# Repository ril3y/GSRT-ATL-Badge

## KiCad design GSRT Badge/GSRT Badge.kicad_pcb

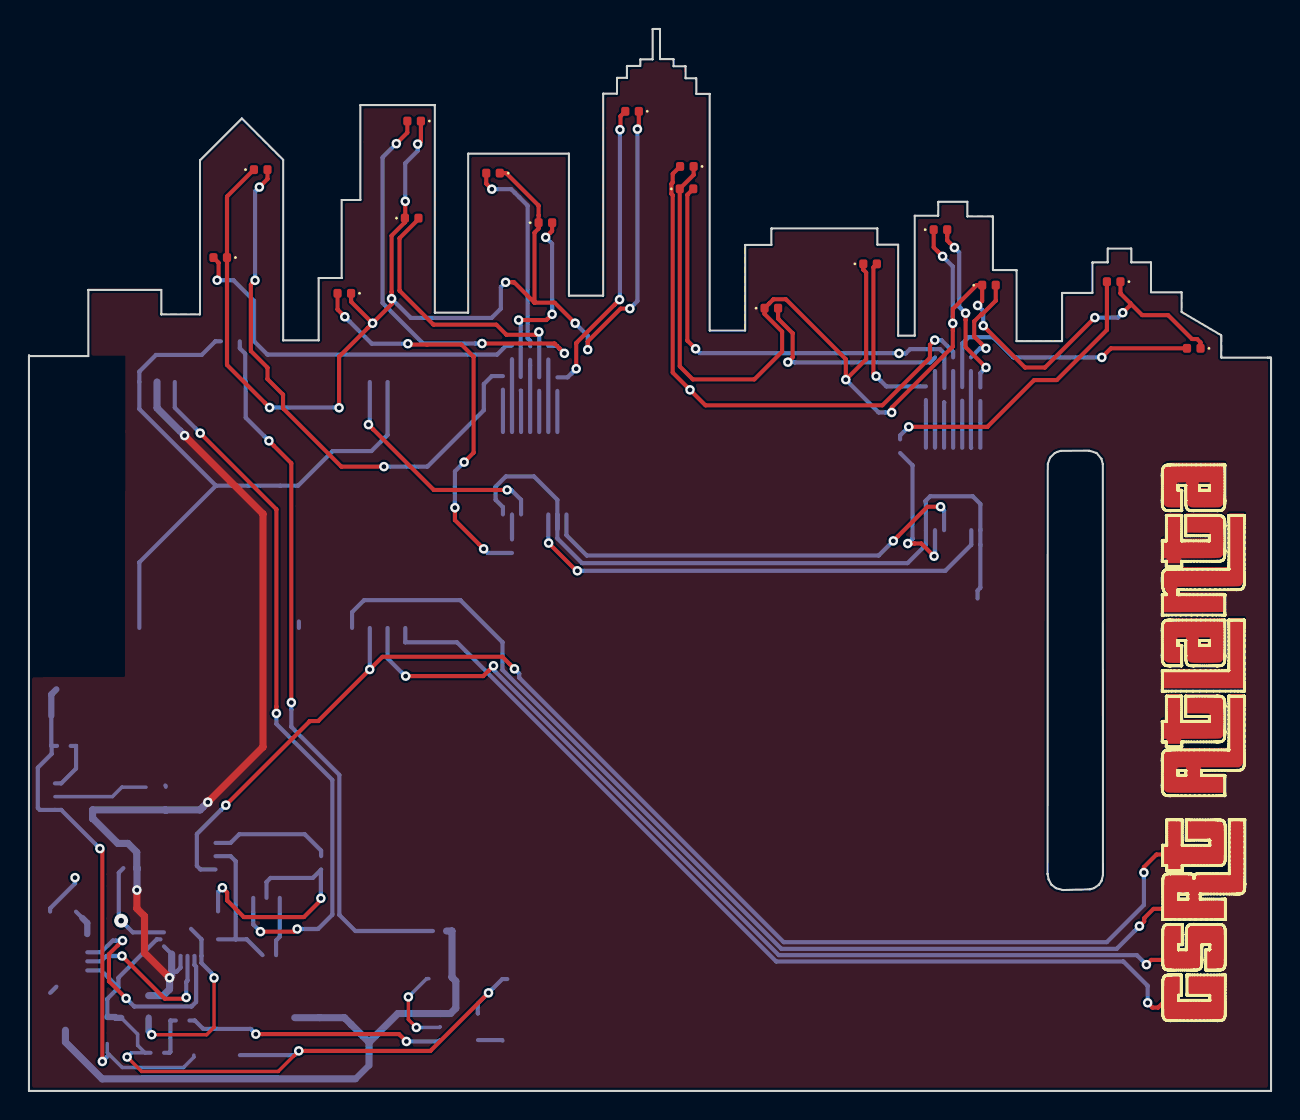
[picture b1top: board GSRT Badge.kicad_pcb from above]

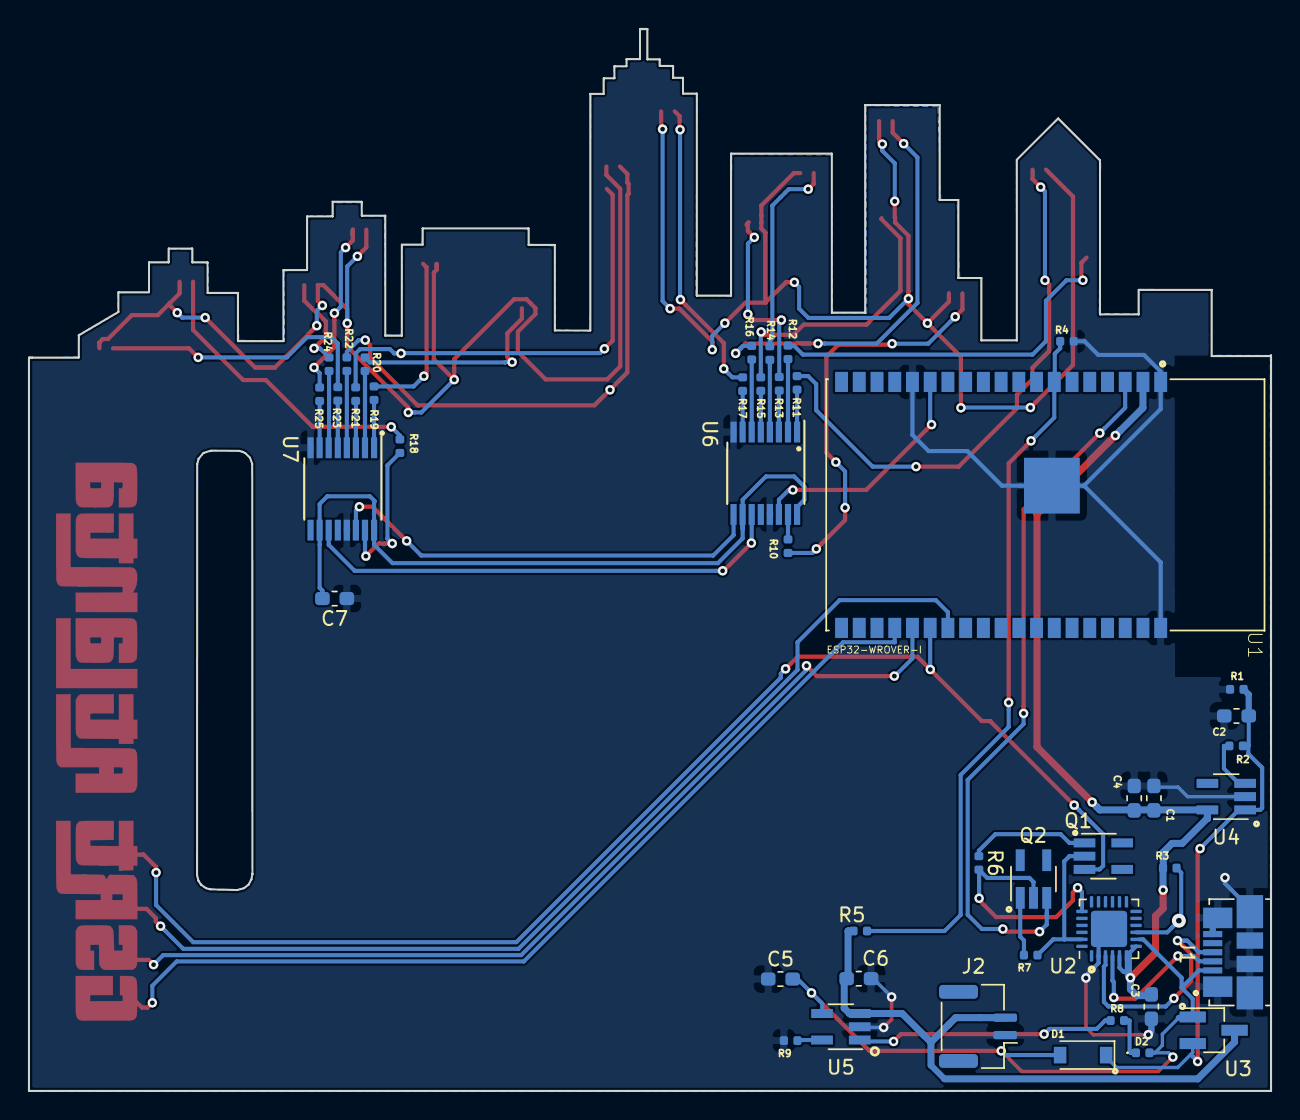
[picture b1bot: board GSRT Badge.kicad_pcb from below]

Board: 2 copper layers, 89.0 x 76.1 mm, 61 parts (45 on the bottom side), 57 nets.

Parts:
C1, C2, C3, C4, C5: 1uf; C_0603_1608Metric_Pad1.05x0.95mm_HandSolder
C6: 10uf; C_0603_1608Metric_Pad1.05x0.95mm_HandSolder
C7: .1uf; C_0603_1608Metric_Pad1.05x0.95mm_HandSolder
D1: MBR120; D_SOD-123
D2: D2; LED_0402_1005Metric
D3, D4, D5, D6, D7, D8, D9, D10, D11, D12, D13, D14, D15, D16, D17, D18: LED; LED_0402_1005Metric
J1: USB_B_Micro; USB_Micro-B_Molex_47346-0001
J2: JST; JST_GH_BM02B-GHS-TBT_1x02-1MP_P1.25mm_Vertical
Q1, Q2: MMBT2222; SOT-23-5_HandSoldering
R1, R2, R4, R5: 100k; R_0402_1005Metric
R3, R9: 4.7k; R_0402_1005Metric
R6, R7: 10k; R_0402_1005Metric
R8: 1k1; R_0402_1005Metric
R10, R11, R12, R13, R14, R15, R16, R17, R18, R19, R20, R21, R22, R23, R24, R25: 200; R_0402_1005Metric
U1: ESP32-WROVER-I; XCVR_ESP32-WROVER-I
U2: CP2104; QFN-24-1EP_4x4mm_P0.5mm_EP2.6x2.6mm
U3: DMG3415U; SOT-23_Handsoldering
U4: AP2112K-3.3; SOT-23-5_HandSoldering
U5: MCP73831-2-OT; SOT-23-5_HandSoldering
U6, U7: 74HC595; TSSOP-16_4.4x5mm_P0.65mm

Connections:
+3.3VA: C1.1, C3.1, C4.1, R3.1, U1.2, U2.5, U2.6, U2.7, U4.5
+3V3: C7.2, U6.10, U6.16, U7.10, U7.16
A13_I35: R4.1, R5.2, U1.7
DTR: Q1.2, R7.2, U2.23
GND: C1.2, C2.2, C3.2, C4.2, C5.1, C6.2, C7.1, J1.5, J1.6, J2.1, R1.2, R4.2, R9.2, U1.1, U1.15, U1.38, U1.39, U2.2, U2.25, U4.2, U5.2, U6.8, U6.13, U7.8, U7.13
GPIO0: Q1.3, U1.25
LED_SHIFT_CLK: U6.11, U7.11
LED_SHIFT_DATA: U1.14, U6.14
unnamed: C2.1, D1.1, R1.1, R2.1, U3.2, U4.1
unnamed: D2.1, R8.1
unnamed: D3.2, R10.2
unnamed: D4.2, R11.2
unnamed: D5.2, R12.2
unnamed: D6.2, R13.2
unnamed: D7.2, R14.2
unnamed: D8.2, R15.2
unnamed: D9.2, R16.2
unnamed: D3.1, D4.1, D5.1, D6.1, D7.1, D8.1, D9.1, D10.1
unnamed: D10.2, R17.2
unnamed: D11.1, D12.1, D13.1, D14.1, D15.1, D16.1, D17.1, D18.1
unnamed: D11.2, R18.2
unnamed: D12.2, R19.2
unnamed: D13.2, R20.2
unnamed: D14.2, R21.2
unnamed: D15.2, R22.2
unnamed: D16.2, R23.2
unnamed: D17.2, R24.2
unnamed: D18.2, R25.2
unnamed: J1.2, U2.4
unnamed: J1.3, U2.3
unnamed: Q1.1, R6.1
unnamed: Q2.1, R7.1
unnamed: R2.2, U4.3
unnamed: R3.2, U2.9
unnamed: R8.2, U5.1
unnamed: R9.1, U5.5
unnamed: R10.1, U6.15
unnamed: R11.1, U6.1
unnamed: R12.1, U6.2
unnamed: R13.1, U6.3
unnamed: R14.1, U6.4
unnamed: R15.1, U6.5
unnamed: R16.1, U6.6
unnamed: R17.1, U6.7
unnamed: R18.1, U7.15
unnamed: R19.1, U7.1
unnamed: R20.1, U7.2
unnamed: R21.1, U7.3
unnamed: R22.1, U7.4
unnamed: R23.1, U7.5
unnamed: R24.1, U7.6
unnamed: R25.1, U7.7
unnamed: U6.9, U7.14
RESET: Q2.3, U1.3
RTS: Q2.2, R6.2, U2.19
VBAT: C6.1, J2.2, R5.1, U3.3, U5.3
VBUS: C5.2, D1.2, D2.2, J1.1, U2.8, U3.1, U5.4

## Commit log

2019-01-25 incremental update
2019-01-26 Test circuit work
